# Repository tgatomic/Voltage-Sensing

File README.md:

# Voltage-Sensing
Voltage sensor for a waterpump

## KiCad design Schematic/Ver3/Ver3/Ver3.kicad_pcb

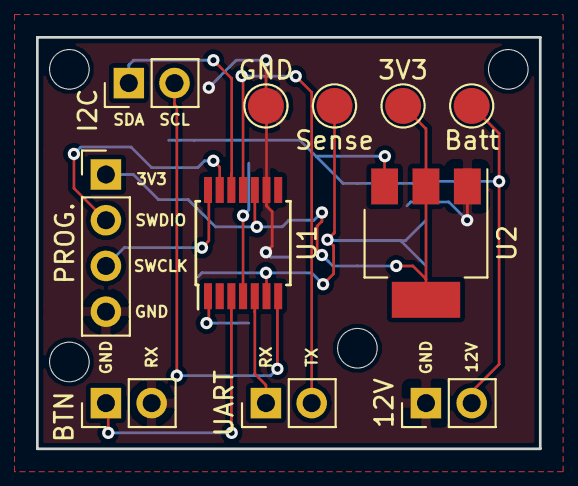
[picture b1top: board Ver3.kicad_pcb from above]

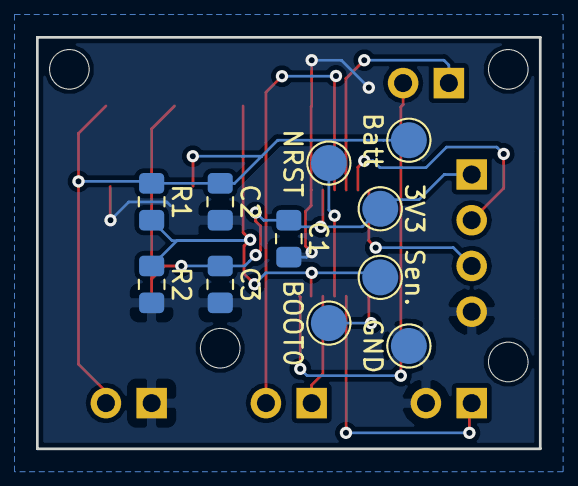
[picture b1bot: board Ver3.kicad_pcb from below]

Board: 2 copper layers, 27.9 x 22.9 mm, 22 parts (11 on the bottom side), 13 nets.

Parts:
3V3, 3V3#2: 3V3; TestPoint_Pad_D2.0mm
12V: 12V; PinHeader_1x02_P2.54mm_Vertical
BOOT0: BOOT0; TestPoint_Pad_D2.0mm
BTN: Button; PinHeader_1x02_P2.54mm_Vertical
Batt: 12V; TestPoint_Pad_D2.0mm
Batt#2: 12V; TestPoint_Pad_D2.0mm
C1, C3: 10uF; C_0805_2012Metric_Pad1.15x1.40mm_HandSolder
C2: 100nF; C_0805_2012Metric_Pad1.15x1.40mm_HandSolder
GND: GND; TestPoint_Pad_D2.0mm
GND#2: GND; TestPoint_Pad_D2.0mm
I2C: I2C; PinHeader_1x02_P2.54mm_Vertical
NRST: NRST; TestPoint_Pad_D2.0mm
PROG.: Prog.; PinHeader_1x04_P2.54mm_Vertical
R1: 10k; R_0805_2012Metric_Pad1.15x1.40mm_HandSolder
R2: 2.74k; R_0805_2012Metric_Pad1.15x1.40mm_HandSolder
Sen.: BattVolt; TestPoint_Pad_D2.0mm
Sense: BattVolt; TestPoint_Pad_D2.0mm
U1: STM32L011D3Px; TSSOP-14_4.4x5mm_P0.65mm
U2: LD1117S33TR_SOT223; SOT-223-3_TabPin2
UART: UART; PinHeader_1x02_P2.54mm_Vertical

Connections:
+3V3: 3V3.1, 3V3#2.1, C1.1, C3.1, PROG..1, U1.10, U2.2
/12Volt: 12V.2, Batt.1, Batt#2.1, C2.1, R1.1, U2.3
/BOOT0: BOOT0.1, U1.1
/BTN: BTN.1, U1.3
/BattVolt: R1.2, R2.1, Sen..1, Sense.1, U1.6
/I2C_SCL: I2C.2, U1.7
/I2C_SDA: I2C.1, U1.12
/NRST: NRST.1, U1.4
/SWCLK: PROG..3, U1.14
/SWDIO: PROG..2, U1.13
/UART_RX: U1.5, UART.1
/UART_TX: U1.11, UART.2
GND: 12V.1, BTN.2, C1.2, C2.2, C3.2, GND.1, GND#2.1, PROG..4, R2.2, U1.9, U2.1

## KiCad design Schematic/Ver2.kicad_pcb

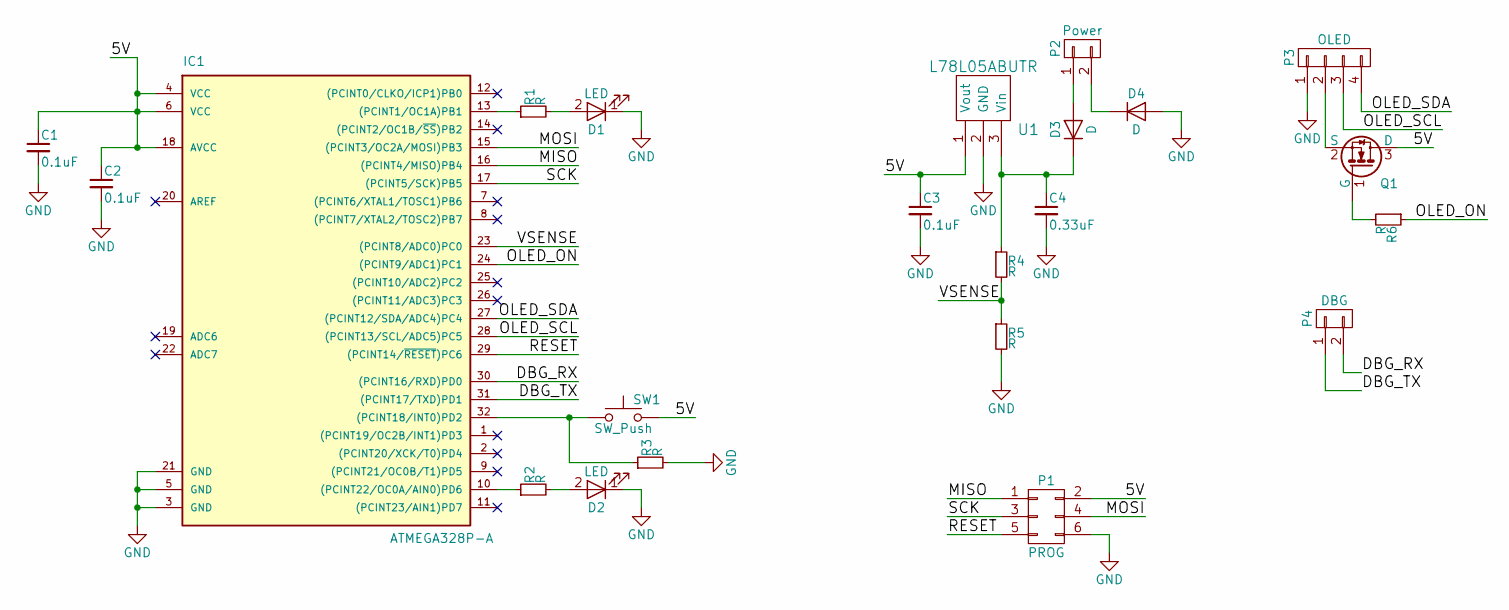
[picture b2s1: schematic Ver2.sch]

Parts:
C1, C2, C3: 0.1uF; C_0805_HandSoldering
C4: 0.33uF; C_0805_HandSoldering
D1, D2: LED; LED_1206
D3, D4: D; D_0805
IC1: ATMEGA328P-A; TQFP-32_7x7mm_Pitch0.8mm; Part number ATMEGA328P-AU
P1: PROG; Pin_Header_Straight_2x03_Pitch2.54mm
P2: Power; 2xSolderpads
P3: OLED; 4xSolderpads
P4: DBG; 2xSolderpads
Q1: 2N7002; SOT-23; Part number NTR5103N
R1, R2, R3, R4, R5, R6: R; R_0805_HandSoldering
SW1: SW_Push; 2xSolderpads
U1: L78L05ABUTR; SOT-89; Part number L78L05ABUTR

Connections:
/5V: C1.1, C2.1, C3.1, IC1.4 (VCC), IC1.6 (VCC), IC1.18 (AVCC), P1.2, Q1.3 (D), SW1.2, U1.1 (Vout)
/DBG_RX: IC1.30 ((PCINT16/RXD)PD0), P4.2
/DBG_TX: IC1.31 ((PCINT17/TXD)PD1), P4.1
/MISO: IC1.16 ((PCINT4/MISO)PB4), P1.1
/MOSI: IC1.15 ((PCINT3/OC2A/MOSI)PB3), P1.4
/OLED_ON: IC1.24 ((PCINT9/ADC1)PC1), R6.1
/OLED_SCL: IC1.28 ((PCINT13/SCL/ADC5)PC5), P3.3
/OLED_SDA: IC1.27 ((PCINT12/SDA/ADC4)PC4), P3.4
/RESET: IC1.29 ((PCINT14/~RESET~)PC6), P1.5
/SCK: IC1.17 ((PCINT5/SCK)PB5), P1.3
/VSENSE: IC1.23 ((PCINT8/ADC0)PC0), R4.2, R5.1
GND: C1.2, C2.2, C3.2, C4.2, D1.1 (K), D2.1 (K), D4.2 (A), IC1.3 (GND), IC1.5 (GND), IC1.21 (GND), P1.6, P3.1, R3.2, R5.2, U1.2 (GND)
unnamed: C4.1, D3.1 (K), R4.1, U1.3 (Vin)
unnamed: D1.2 (A), R1.2
unnamed: D2.2 (A), R2.2
unnamed: D3.2 (A), P2.1
unnamed: D4.1 (K), P2.2
unnamed: IC1.10 ((PCINT22/OC0A/AIN0)PD6), R2.1
unnamed: IC1.13 ((PCINT1/OC1A)PB1), R1.1
unnamed: IC1.32 ((PCINT18/INT0)PD2), R3.1, SW1.1
unnamed: P3.2, Q1.2 (S)
unnamed: Q1.1 (G), R6.2

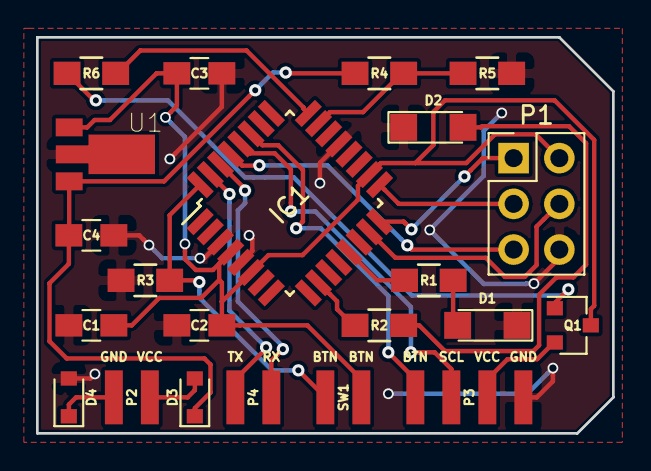
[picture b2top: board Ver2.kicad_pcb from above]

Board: 2 copper layers, 32.0 x 22.0 mm, 22 parts (0 on the bottom side), 22 nets.

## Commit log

2017-02-10 Updated the readme with short description
2017-02-10 First version of schematic and footprint placement
2017-02-11 Created a Atmel project and started with initcode
    Got UART and OLED display to work. Also created a welcome message
    screen.
2017-02-12 Can now print Volts and time left
2017-02-12 Changed to hod data in struct instead
    Also made a separate function for the conversion to ascii for the print
    function.
2017-02-12 Added the tracks and completed the design
    ordered the cars form OSH park
2017-02-13 Added ADC fuction, created init and made the code ready for the final verison
    The rest must be tested mounted on the PCB
2017-05-03 Changed Partnumber on a resistor
    Had to change to another component when ordering because component was
    out of stock.
2019-03-27 created a cube project and created a new schematic
